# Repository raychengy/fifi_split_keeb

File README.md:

# Fifi Keyboard 🐶 ⌨️
- [Fifi Keyboard](#fifi-keyboard-🐶-⌨️)
  - [TODO](#todo)
  - [Bill of Materials (BOM)](docs/BOM.md)
  - [Building Instructions](docs/BuildInstructions.md)
    - [Build Keyboard](docs/BuildInstructions.md#build-keyboard)
    - [Build Firmware](docs/BuildInstructions.md#build-firmware)

The Fifi keyboard, named after my [🐶](assets/fifi.gif), is a split keyboard with 3x5 column staggered keys and 3 thumb keys, based on foostan's mini-[crkbd](https://github.com/foostan/crkbd/) schematic and thomasbaart's [kyria](https://github.com/splitkb/kyria) layout.

The goal of this project was to build a split keyboard that fits perfectly for the [miryoku](https://github.com/manna-harbour/miryoku) layout with the minimalist style of mini-crkbd and have the aggressive column staggered keys found in kyria. The PCB is reversible, meaning you'll need two of the same PCB to create a full keyboard. It is my first attempt in PCB board design.

## TODO
- Add tent puck support
- Add an additional key in the thumb cluster (support for rotorary encoder)
- Add 3D-printed case

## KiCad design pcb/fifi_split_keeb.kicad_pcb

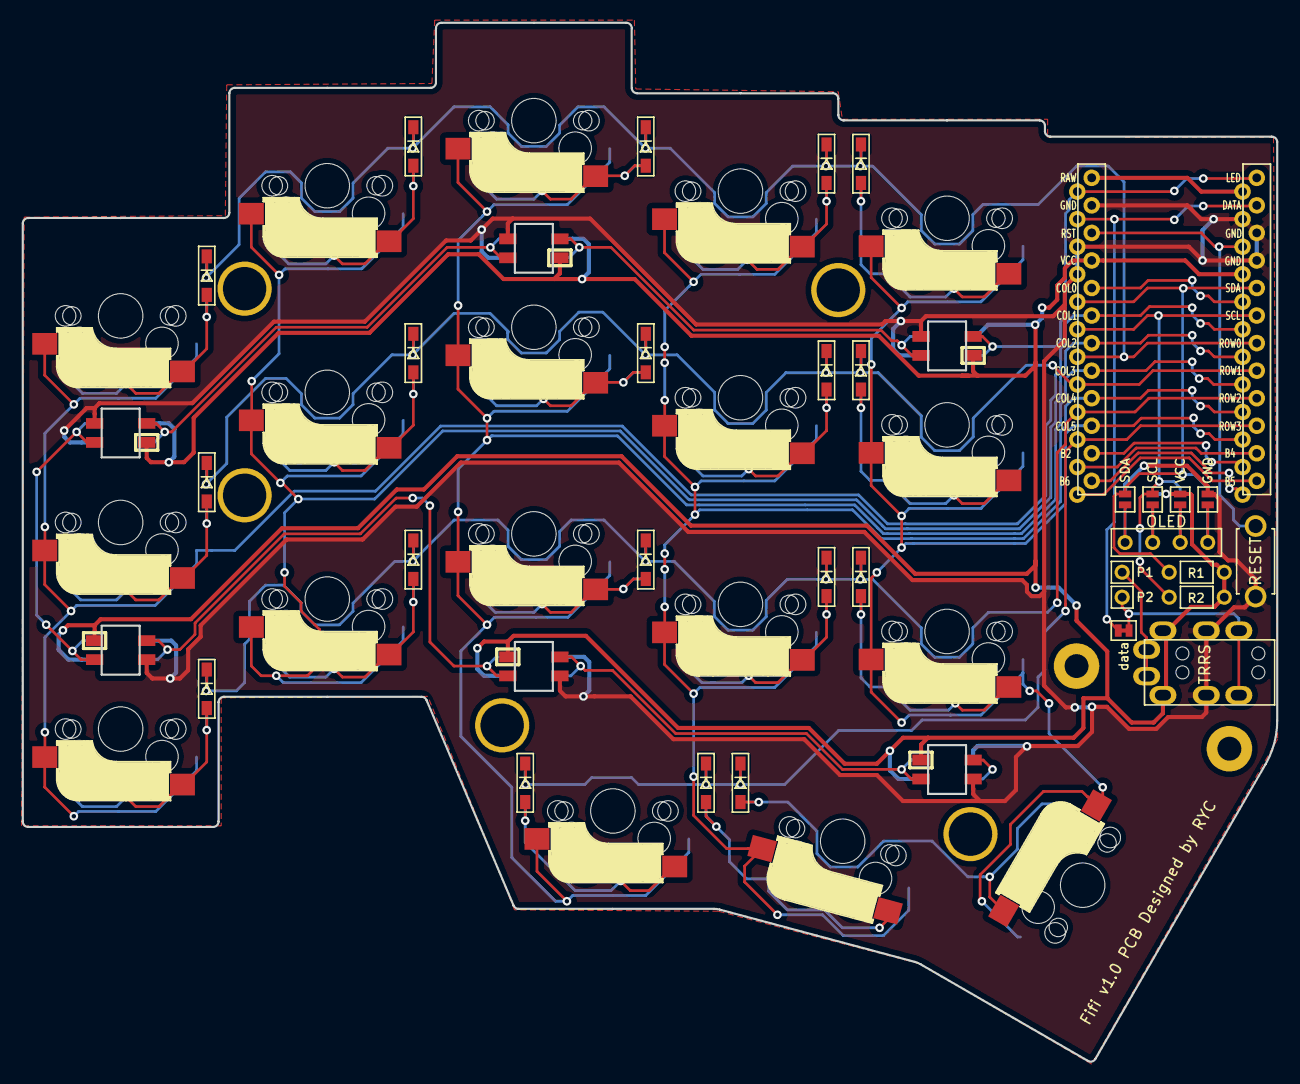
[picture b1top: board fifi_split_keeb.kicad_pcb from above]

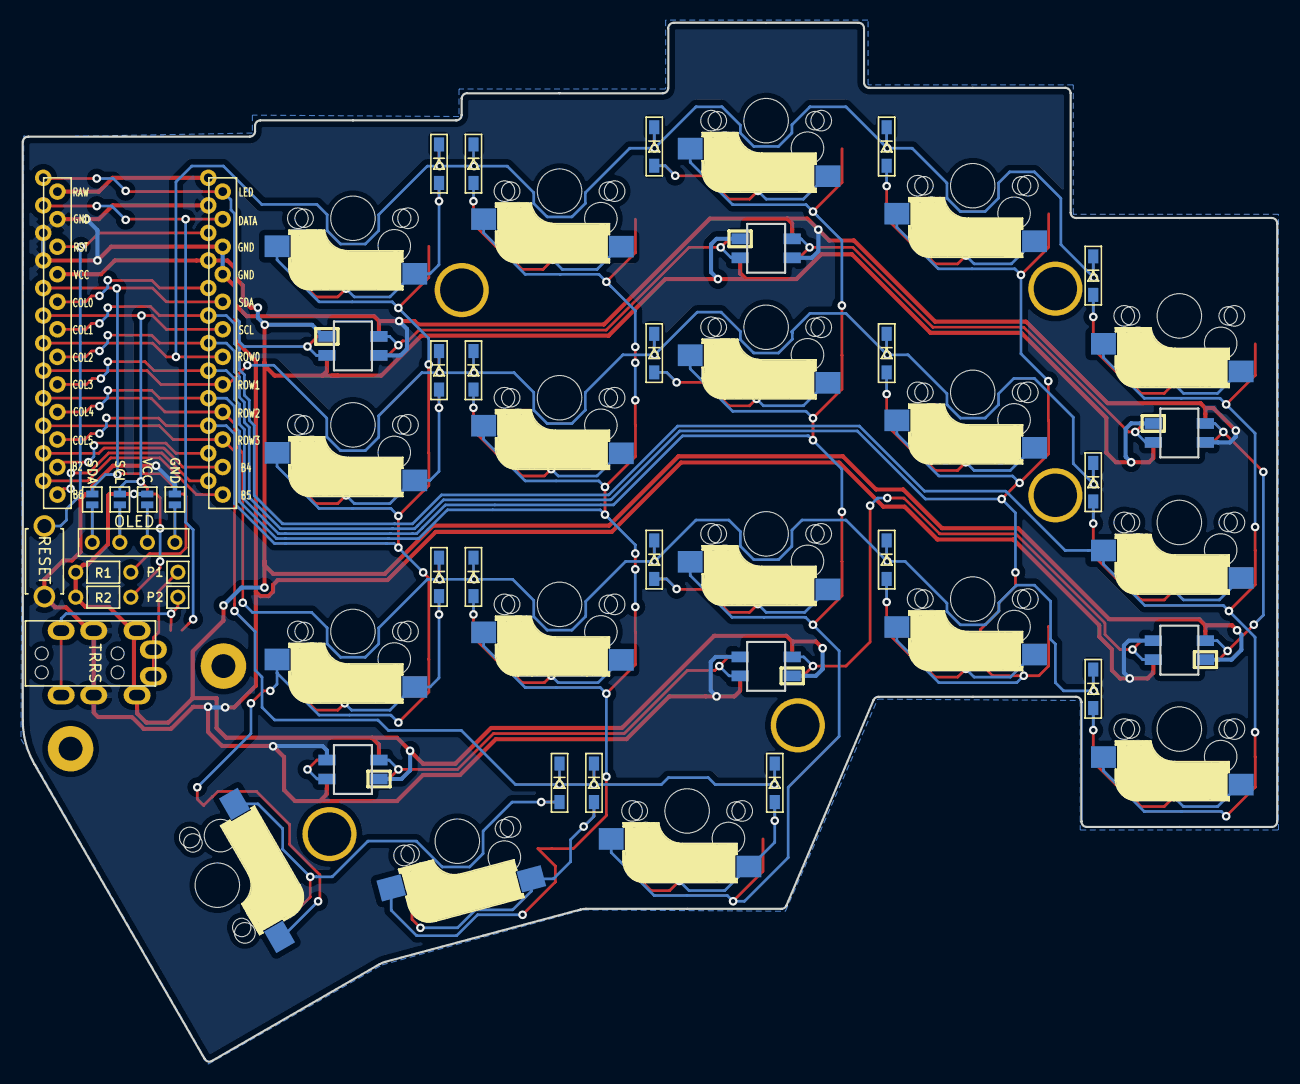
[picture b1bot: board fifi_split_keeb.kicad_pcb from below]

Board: 2 copper layers, 115.7 x 95.8 mm, 59 parts (4 on the bottom side), 45 nets.

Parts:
D1, D2, D3, D4, D5, D6, D7, D8, D9, D10, D11, D12, D13, D14, D15, D16, D17, D18: D; D3_SMD
J1: TRRS-Barrel; MJ-4PP-9
J2: OLED
JP1, JP8: GND; Jumper
JP2, JP7: VCC; Jumper
JP3, JP6: SCL; Jumper
JP4, JP5: SDA; Jumper
JP9: data; JPC2
L19, L20, L21, L22, L23, L24: SK6812MINI; SK6812MINI_rev
P1, P2: i2c-pin; 1pin_conn
R1, R2: R
RSW1: SW_PUSH; ResetSW
SW1, SW2, SW3, SW4, SW5, SW6, SW7, SW8, SW9, SW10, SW11, SW12, SW13, SW14, SW15, SW16, SW17: SW_PUSH; CherryMX_MidHeight_Hotswap
SW18: SW_PUSH; CherryMX_MidHeight_Hotswap_1.5u
U1: ProMicro; ProMicro_v2

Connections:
GND: J1.C, JP1.2, JP8.2, L19.2, L20.2, L21.2, L22.2, L23.2, L24.2, RSW1.2, U1.3, U1.4, U1.23
LED: L21.3, U1.1
unnamed: D1.2, SW1.2
unnamed: D2.2, SW2.2
unnamed: D3.2, SW3.2
unnamed: D4.2, SW4.2
unnamed: D5.2, SW5.2
unnamed: D6.2, SW6.2
unnamed: D7.2, SW7.2
unnamed: D8.2, SW8.2
unnamed: D9.2, SW9.2
unnamed: D10.2, SW10.2
unnamed: D11.2, SW11.2
unnamed: D12.2, SW12.2
unnamed: D13.2, SW13.2
unnamed: D14.2, SW14.2
unnamed: D15.2, SW15.2
unnamed: D16.2, SW16.2
unnamed: D17.2, SW17.2
unnamed: D18.2, SW18.2
unnamed: J1.A, P1.1
unnamed: J1.B, JP9.2, P2.1
unnamed: J2.1, JP4.1, JP8.1
unnamed: J2.2, JP3.1, JP7.1
unnamed: J2.3, JP2.1, JP6.1
unnamed: J2.4, JP1.1, JP5.1
unnamed: L19.1, L22.3
unnamed: L19.3, L20.1
unnamed: L20.3, L21.1
unnamed: L22.1, L23.3
unnamed: L23.1, L24.3
SCL: JP3.2, JP6.2, R2.2, U1.6
SDA: JP4.2, JP5.2, R1.2, U1.5
VCC: J1.D, JP2.2, JP7.2, L19.4, L20.4, L21.4, L22.4, L23.4, L24.4, R1.1, R2.1, U1.21
col0: SW1.1, SW6.1, SW11.1, U1.19
col1: SW2.1, SW7.1, SW12.1, U1.18
col2: SW3.1, SW8.1, SW13.1, SW16.1, U1.17
col3: SW4.1, SW9.1, SW14.1, SW17.1, U1.16
col4: SW5.1, SW10.1, SW15.1, SW18.1, U1.15
data: JP9.1, U1.2
reset: RSW1.1, U1.22
row0: D1.1, D2.1, D3.1, D4.1, D5.1, U1.7
row1: D6.1, D7.1, D8.1, D9.1, D10.1, U1.8
row2: D11.1, D12.1, D13.1, D14.1, D15.1, U1.9
row3: D16.1, D17.1, D18.1, U1.10

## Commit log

2021-01-05 Initial release of fifi keeb with documentations
2021-01-11 Added github action workflow to build gerber files
2021-01-14 Added top-plate gerber file & updated .dxf file
2021-09-23 Updated readme w/ wishlist & btm plate gerber zip
2022-06-13 Update miryoku_qmk git repository URL to its new location
    See manna-harbour/qmk_firmware@b6ddc6c6166a89a9ec50ef4592a327badc5d0b1b
